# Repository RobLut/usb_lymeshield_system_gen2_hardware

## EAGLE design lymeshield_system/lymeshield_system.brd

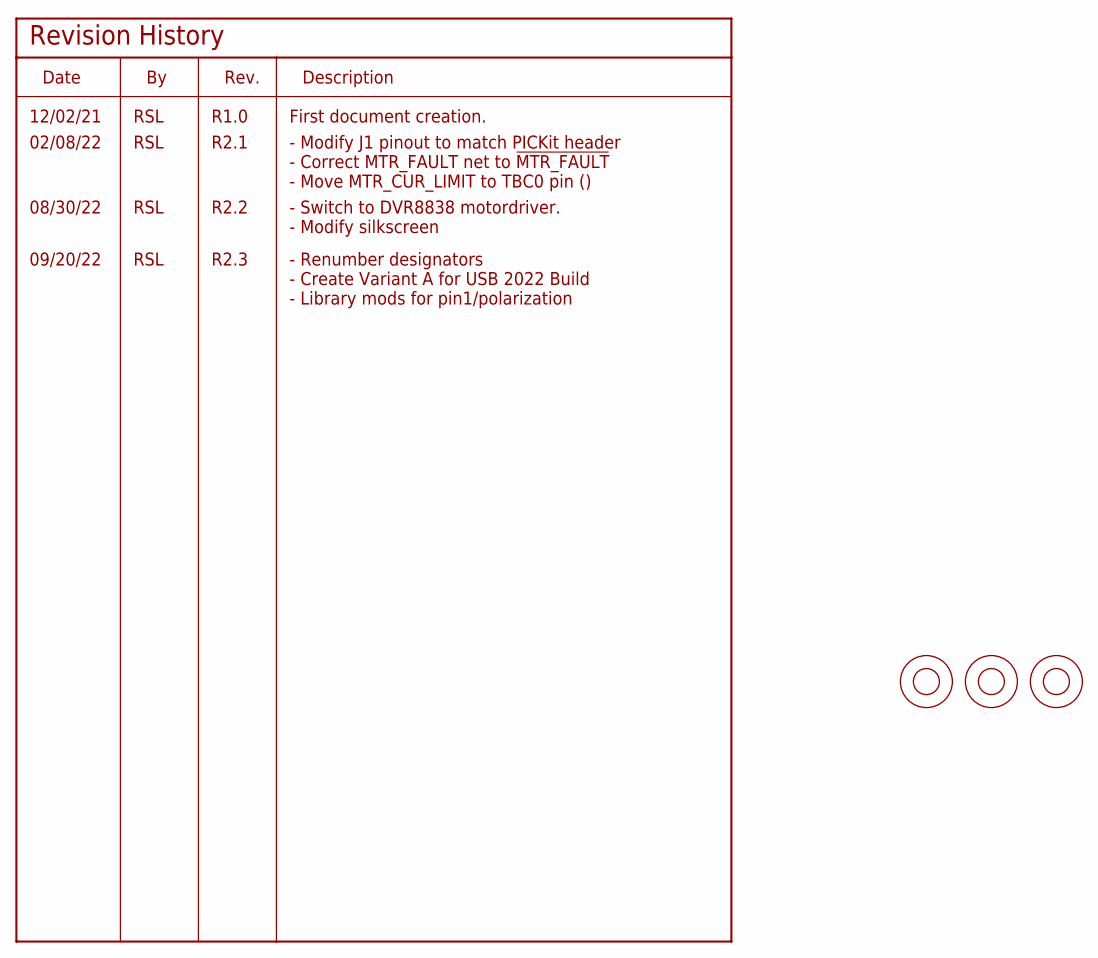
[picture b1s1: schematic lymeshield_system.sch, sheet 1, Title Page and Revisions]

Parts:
FID1, FID2, FID3: FIDUCIAL_1MM_TOP_BOTTOM

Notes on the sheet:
12/02/21
RSL
R1.0
First document creation.
02/08/22
R2.1
- Modify J1 pinout to match PICKit header - Correct MTR_FAULT net to !MTR_FAULT - Move MTR_CUR_LIMIT to TBC0 pin ()
08/30/22
R2.2
- Switch to DVR8838 motordriver. - Modify silkscreen
09/20/22
R2.3
- Renumber designators - Create Variant A for USB 2022 Build - Library mods for pin1/polarization

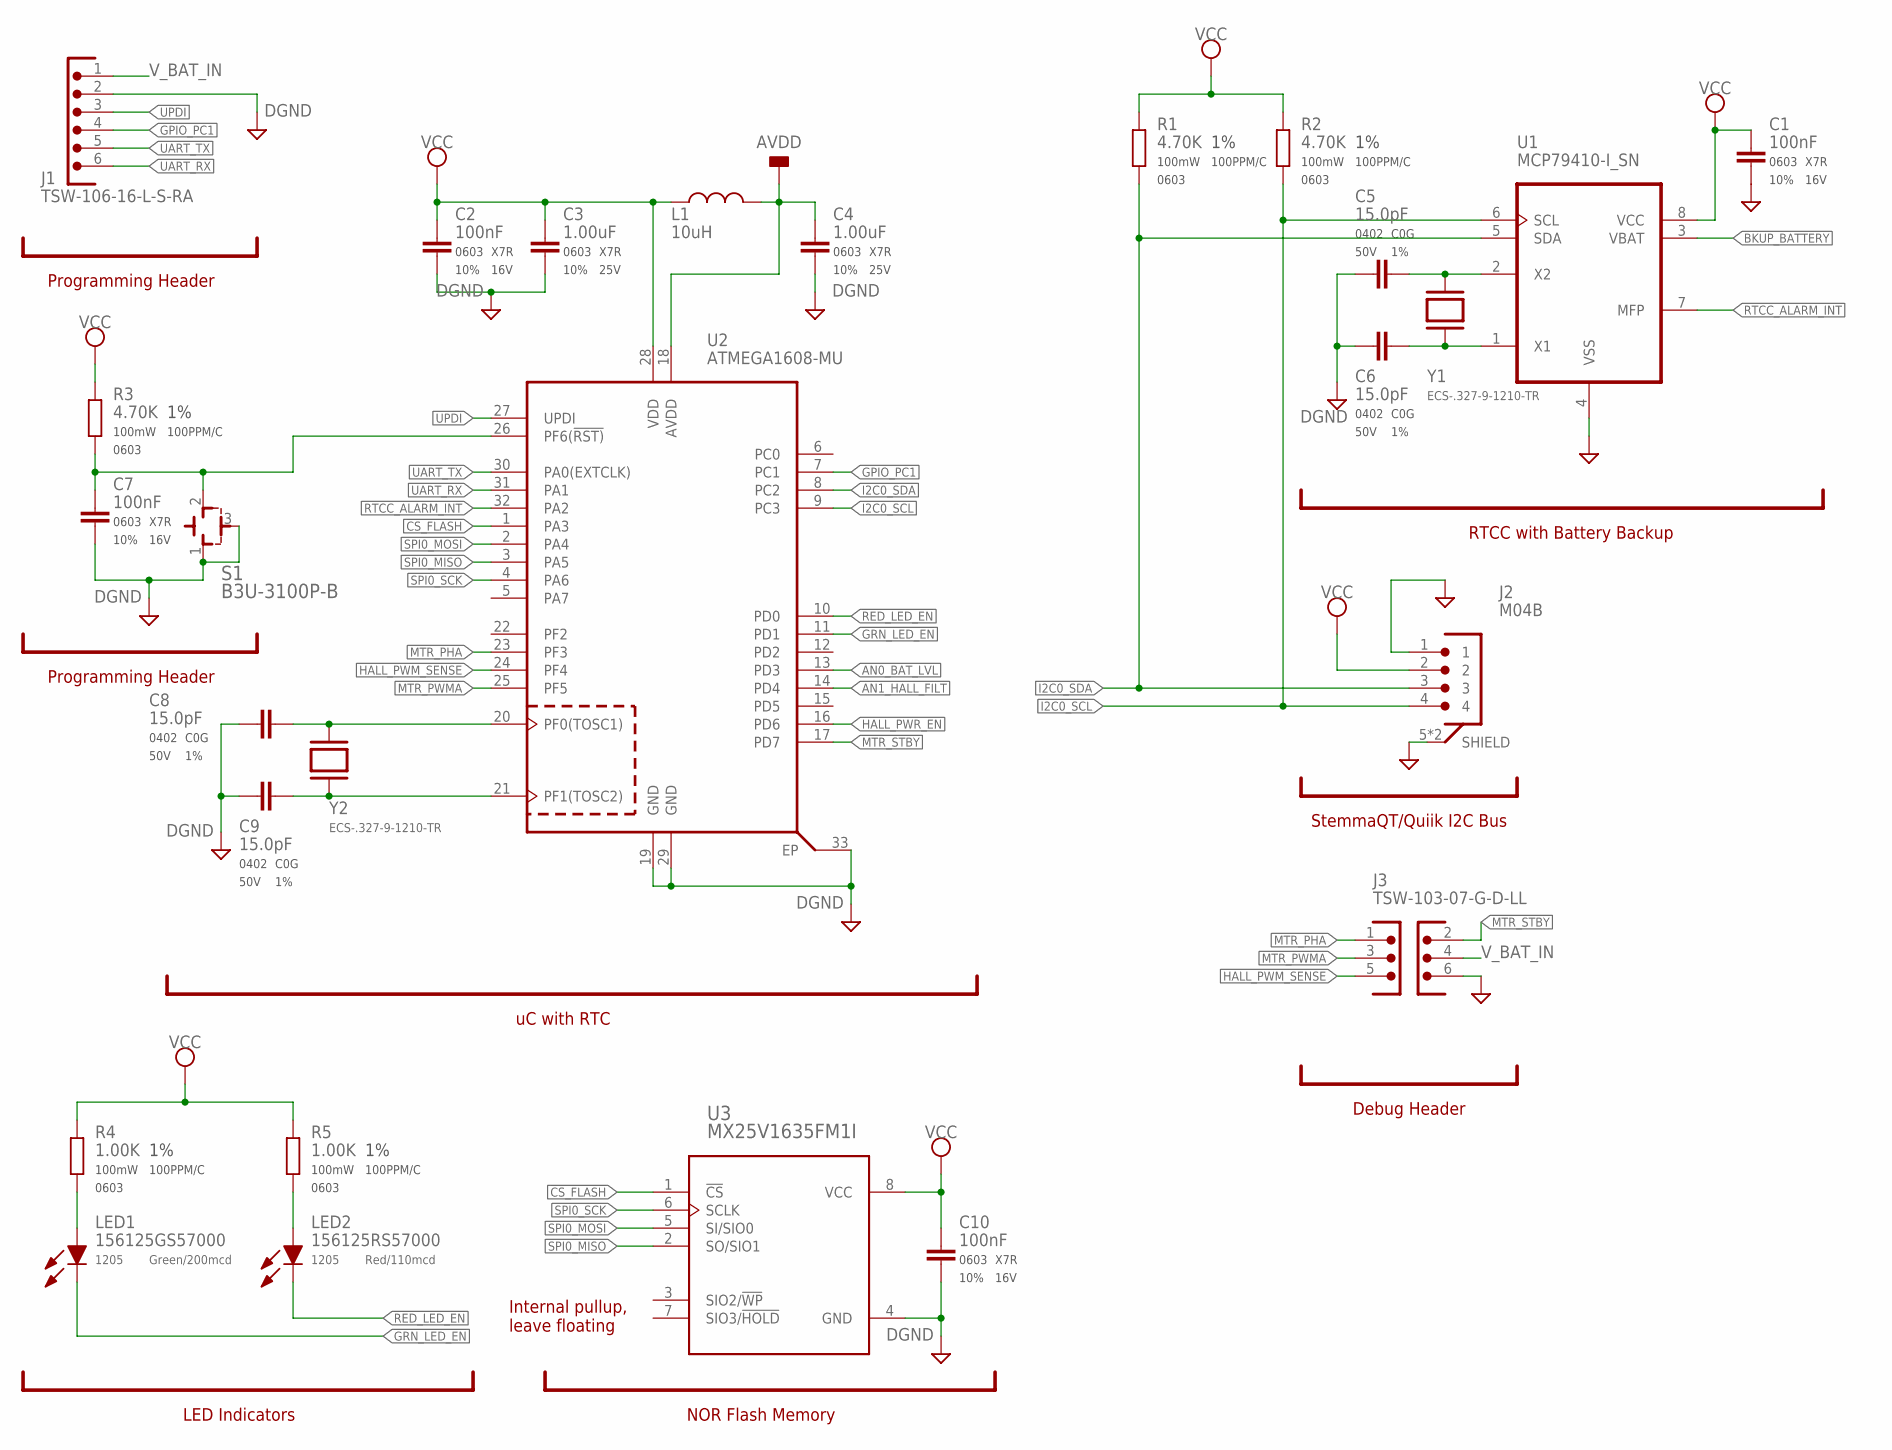
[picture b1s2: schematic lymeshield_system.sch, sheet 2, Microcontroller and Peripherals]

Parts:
C1, C2, C7, C10: 100nF; CAPC_0603_1608X90N
C3, C4: 1.00uF; CAPC_0603_1608X90N
C5, C6, C8, C9: 15.0pF; CAPC_0402_1005X55N
J1: TSW-106-16-L-S-RA; HDR-100MIL-1X6-THRU-RA
J2: M04B; SM04B-SRSS-TB(LFSN)
J3: TSW-103-07-G-D-LL; HDRV6W64P254_2X3_762X495X838P
L1: 10uH; INDC1608X90N
LED1: 156125GS57000; LEDC3212X120N
LED2: 156125RS57000; LEDC3212X120N
R1, R2, R3: 4.70K; R0603K
R4, R5: 1.00K; R0603K
S1: B3U-3100P-B
U1: MCP79410-I_SN; SOIC127P600X175-8N
U2: ATMEGA1608-MU; QFN50P500X500X90-33N
U3: MX25V1635FM1I; SOIC127P600X175-8N
Y1, Y2: ECS-.327-9-1210-TR; XTAL_ECS-.327-9-1210-TR

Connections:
!CS_FLASH: U2.1 (PA3), U3.1 (!CS)
!GRN_LED_EN: LED1.1 (K), U2.11 (PD1)
!MTR_STBY: J3.2, U2.17 (PD7); also elsewhere on the board
!RED_LED_EN: LED2.1 (K), U2.10 (PD0)
!RST: C7.1, R3.2, S1.2 (NO), U2.26 (PF6(!RST))
AN0_BAT_LVL: U2.13 (PD3); also elsewhere on the board
AN1_HALL_FILT: U2.14 (PD4); also elsewhere on the board
AVDD: C4.1, L1.2, U2.18 (AVDD)
BKUP_BATTERY: U1.3 (VBAT); also elsewhere on the board
DGND: C1.2, C2.2, C3.2, C4.2, C5.2, C6.2, C7.2, C8.2, C9.2, C10.2, J1.2, J2.1, J2.5 (SHIELD), J2.6 (SHIELD), J3.6, S1.1 (COM), S1.3 (COM1), U1.4 (VSS), U2.19 (GND), U2.29 (GND), U2.33 (EP), U3.4 (GND); also elsewhere on the board
GPIO_PC1: J1.4, U2.7 (PC1)
HALL_PWM_SENSE: J3.5, U2.24 (PF4); also elsewhere on the board
HALL_PWR_EN: U2.16 (PD6); also elsewhere on the board
I2C0_SCL: J2.4, R2.2, U1.6 (SCL), U2.9 (PC3)
I2C0_SDA: J2.3, R1.2, U1.5 (SDA), U2.8 (PC2)
MTR_PHA: J3.1, U2.23 (PF3); also elsewhere on the board
MTR_PWMA: J3.3, U2.25 (PF5); also elsewhere on the board
unnamed: C8.1, U2.20 (PF0(TOSC1)), Y2.1
unnamed: C5.1, U1.2 (X2), Y1.1
unnamed: LED1.2 (A), R4.2
unnamed: LED2.2 (A), R5.2
unnamed: C9.1, U2.21 (PF1(TOSC2)), Y2.2
unnamed: C6.1, U1.1 (X1), Y1.2
RTCC_ALARM_INT: U1.7 (MFP), U2.32 (PA2)
SPI0_MISO: U2.3 (PA5), U3.2 (SO/SIO1)
SPI0_MOSI: U2.2 (PA4), U3.5 (SI/SIO0)
SPI0_SCK: U2.4 (PA6), U3.6 (SCLK)
UART_RX: J1.6, U2.31 (PA1)
UART_TX: J1.5, U2.30 (PA0(EXTCLK))
UPDI: J1.3, U2.27 (UPDI)
VCC: C1.1, C2.1, C3.1, C10.1, J2.2, L1.1, R1.1, R2.1, R3.1, R4.1, R5.1, U1.8 (VCC), U2.28 (VDD), U3.8 (VCC); also elsewhere on the board
V_BAT_IN: J1.1, J3.4; also elsewhere on the board

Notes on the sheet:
Internal pullup, leave floating
StemmaQT/Quiik I2C Bus
NOR Flash Memory
RTCC with Battery Backup
Programming Header
LED Indicators
uC with RTC
Debug Header

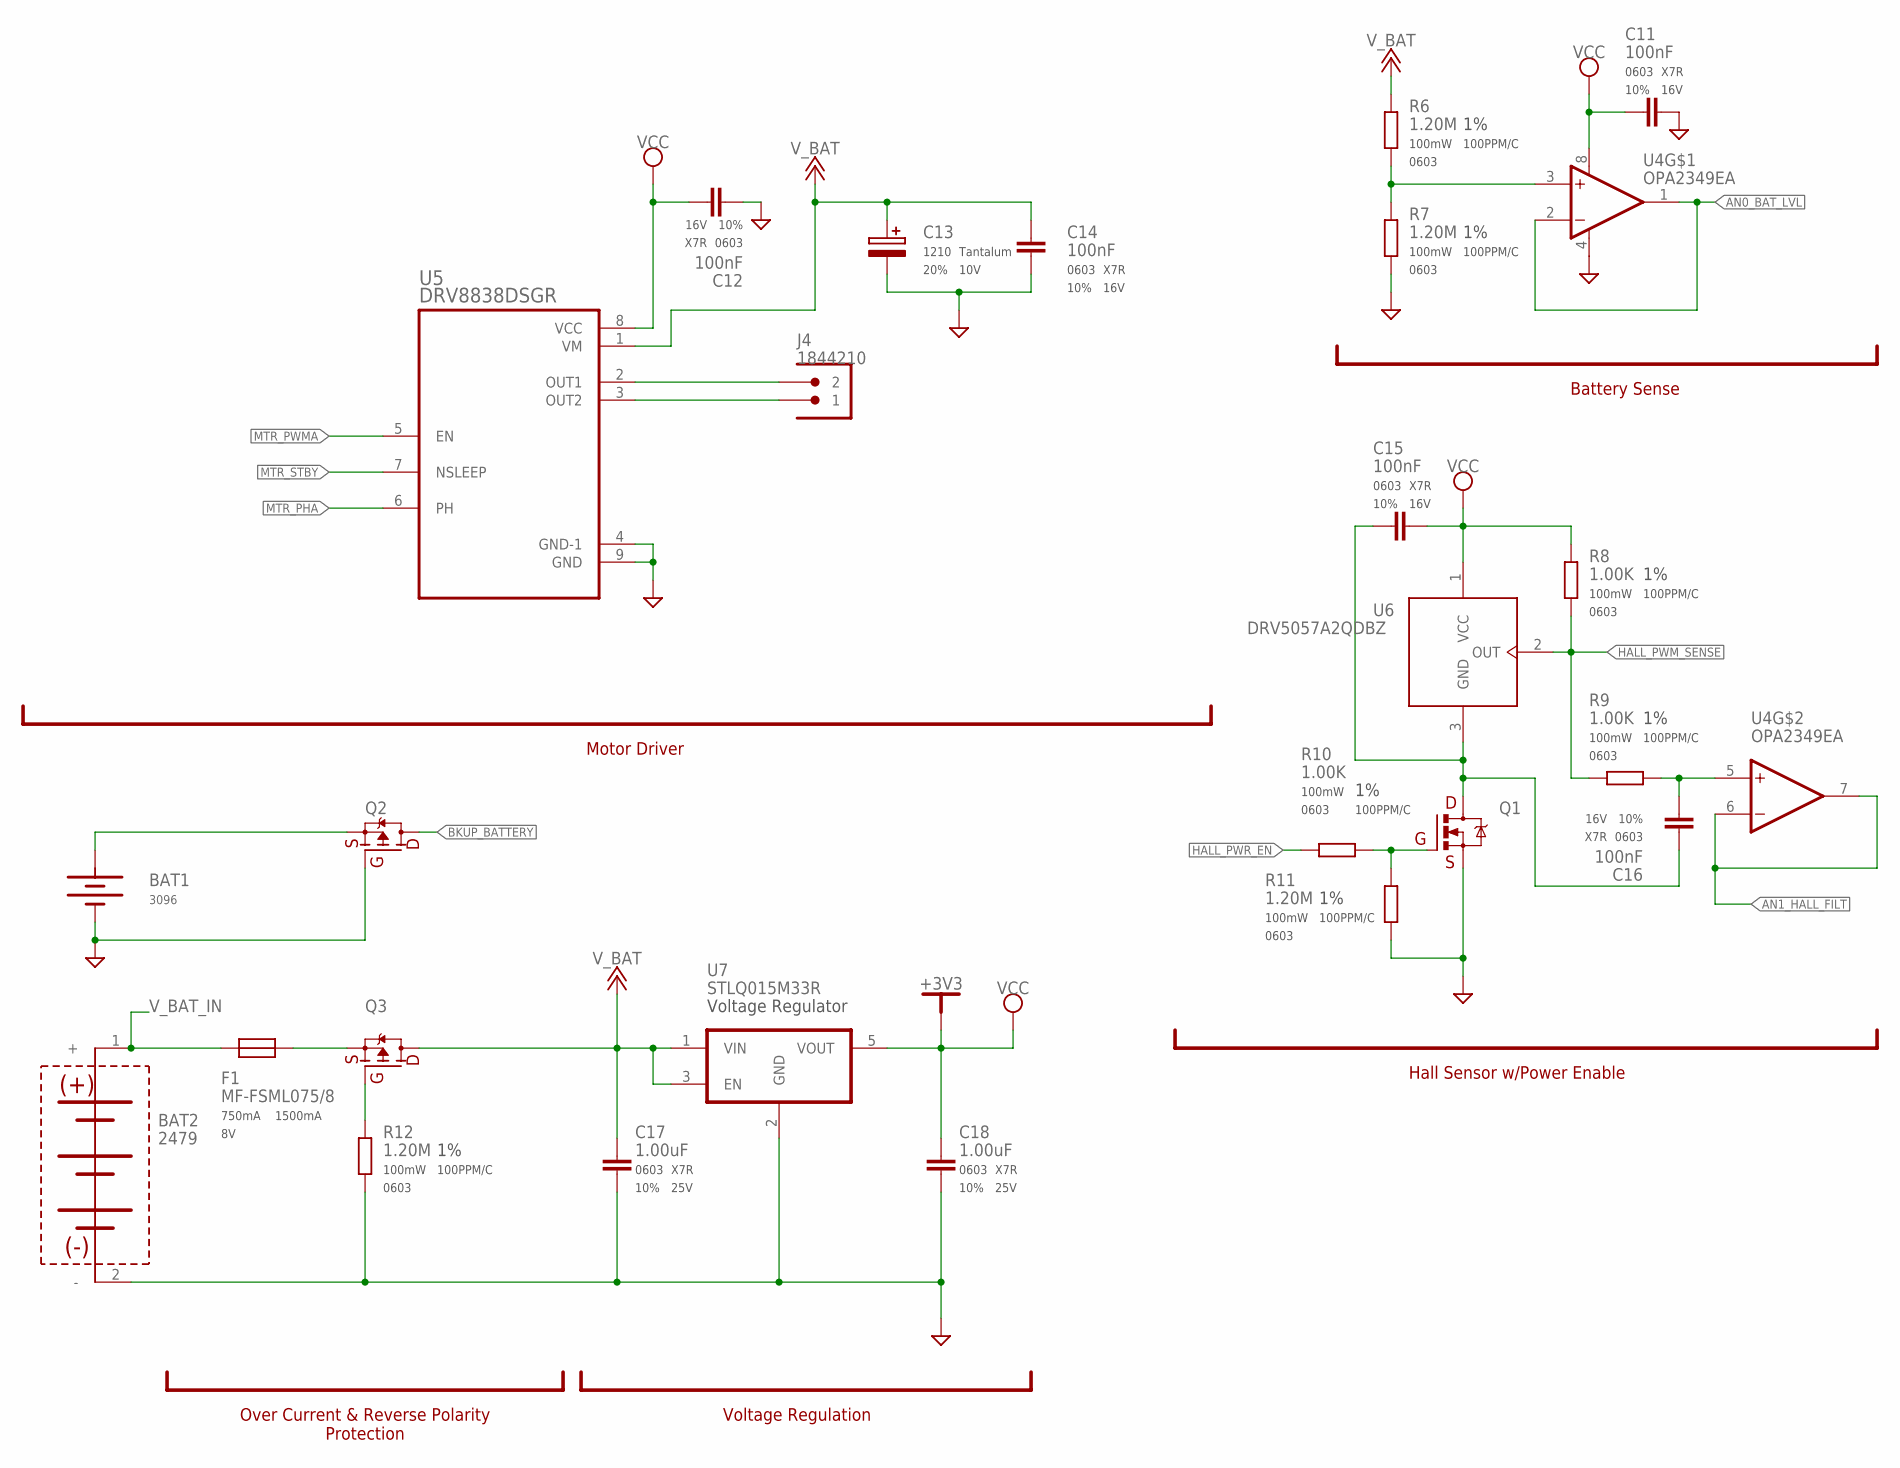
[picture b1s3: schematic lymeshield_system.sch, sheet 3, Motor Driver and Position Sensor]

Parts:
BAT1: 3096
BAT2: 2479
C11, C12, C14, C15, C16: 100nF; CAPC_0603_1608X90N
C13: TAJB226M010RNJ; PCAPC_1210
C17, C18: 1.00uF; CAPC_0603_1608X90N
F1: MF-FSML075/8; FUSC1608X70N
J4: 1844210; 1844210-2-3.50
Q1: FDN5632N-F085-FDN5632N_F085; SOT-23
Q2, Q3: PMOS_DMP2035U-7; SOT-23
R6, R7, R11, R12: 1.20M; R0603K
R8, R9, R10: 1.00K; R0603K
U4: OPA2349EA; SOT65P280X145-8N
U5: DRV8838DSGR; SON50P200X200X80-9N
U6: DRV5057A2QDBZ; SOT95P237X112-3N
U7: STLQ015M33R; SOT23-5L

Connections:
!MTR_STBY: U5.7 (NSLEEP); also elsewhere on the board
AN0_BAT_LVL: U4.1 (OUT), U4.2 (-IN); also elsewhere on the board
AN1_HALL_FILT: U4.6 (-IN), U4.7 (OUT); also elsewhere on the board
BKUP_BATTERY: Q2.1 (D); also elsewhere on the board
DGND: BAT1.1 (-), BAT1.3 (-), BAT2.2 (-), C11.1, C12.2, C13.2 (-), C14.2, C17.2, C18.2, Q1.2 (S), Q2.3 (G), R7.2, R11.2, R12.2, U4.4 (V-), U5.4 (GND-1), U5.9 (GND), U7.2 (GND); also elsewhere on the board
HALL_PWM_SENSE: R8.2, R9.1, U6.2 (OUT); also elsewhere on the board
HALL_PWR_EN: R10.1; also elsewhere on the board
MTR_PHA: U5.6 (PH); also elsewhere on the board
MTR_PWMA: U5.5 (EN); also elsewhere on the board
unnamed: Q1.3 (G), R10.2, R11.1
unnamed: Q3.3 (G), R12.1
unnamed: BAT1.2 (+), Q2.2 (S)
unnamed: R6.2, R7.1, U4.3 (+IN)
unnamed: F1.2, Q3.2 (S)
unnamed: C16.1, R9.2, U4.5 (+IN)
unnamed: C15.2, C16.2, Q1.1 (D), U6.3 (GND)
OUTA1: J4.P$2 (2), U5.2 (OUT1)
OUTA2: J4.P$1 (1), U5.3 (OUT2)
VCC: C11.2, C12.1, C15.1, C18.1, R8.1, U4.8 (V+), U5.8 (VCC), U6.1 (VCC), U7.5 (VOUT); also elsewhere on the board
V_BAT: C13.1 (+), C14.1, C17.1, Q3.1 (D), R6.1, U5.1 (VM), U7.1 (VIN), U7.3 (EN)
V_BAT_IN: BAT2.1 (+), F1.1; also elsewhere on the board

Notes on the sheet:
Hall Sensor w/Power Enable
Voltage Regulation
Over Current & Reverse Polarity Protection
Motor Driver
Battery Sense

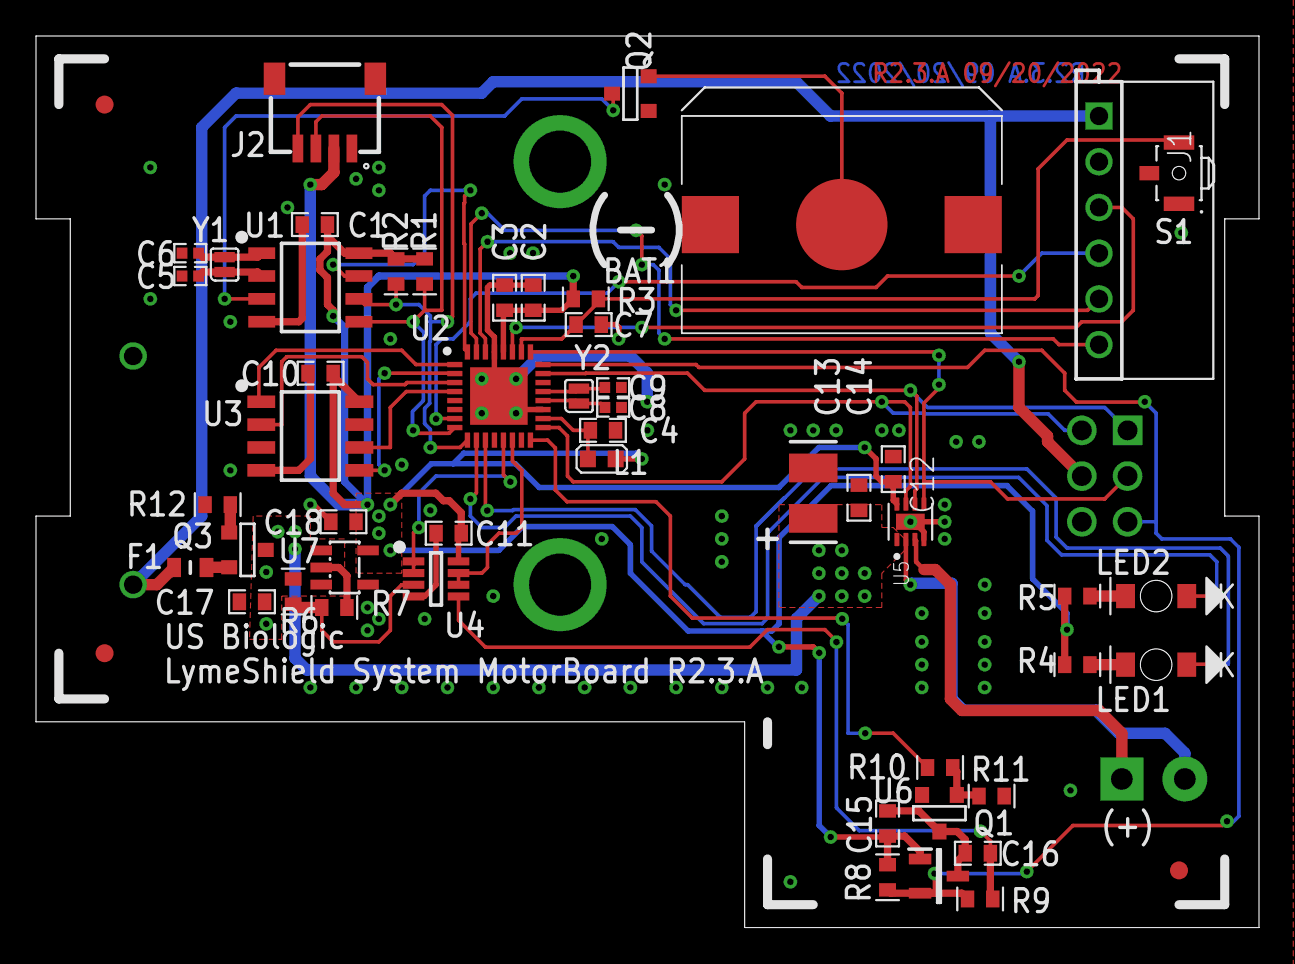
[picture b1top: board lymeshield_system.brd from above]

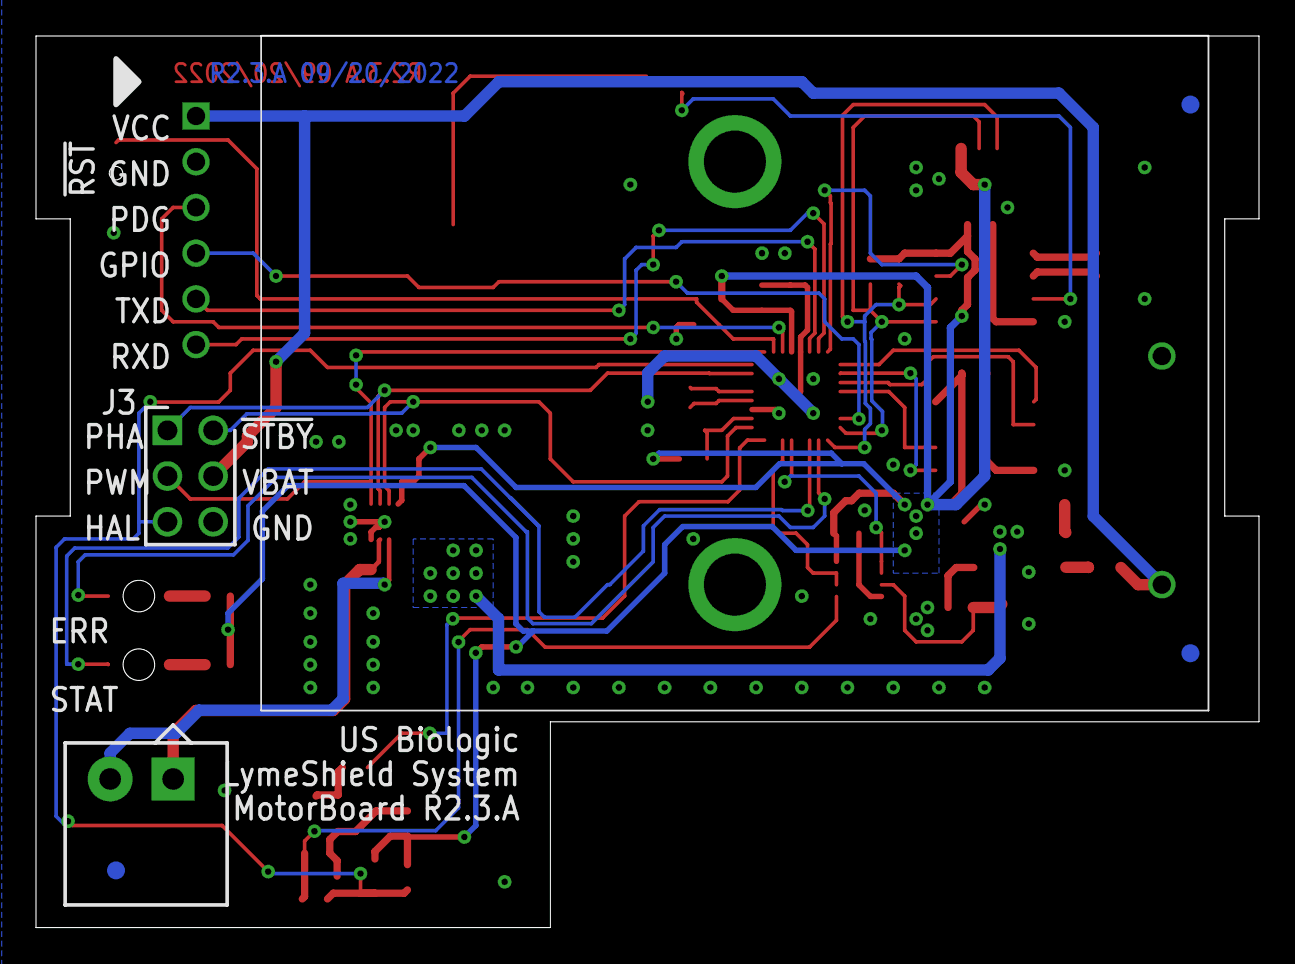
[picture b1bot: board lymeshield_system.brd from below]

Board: 2 copper layers, 67.9 x 49.5 mm, 56 parts (3 on the bottom side), 42 nets.

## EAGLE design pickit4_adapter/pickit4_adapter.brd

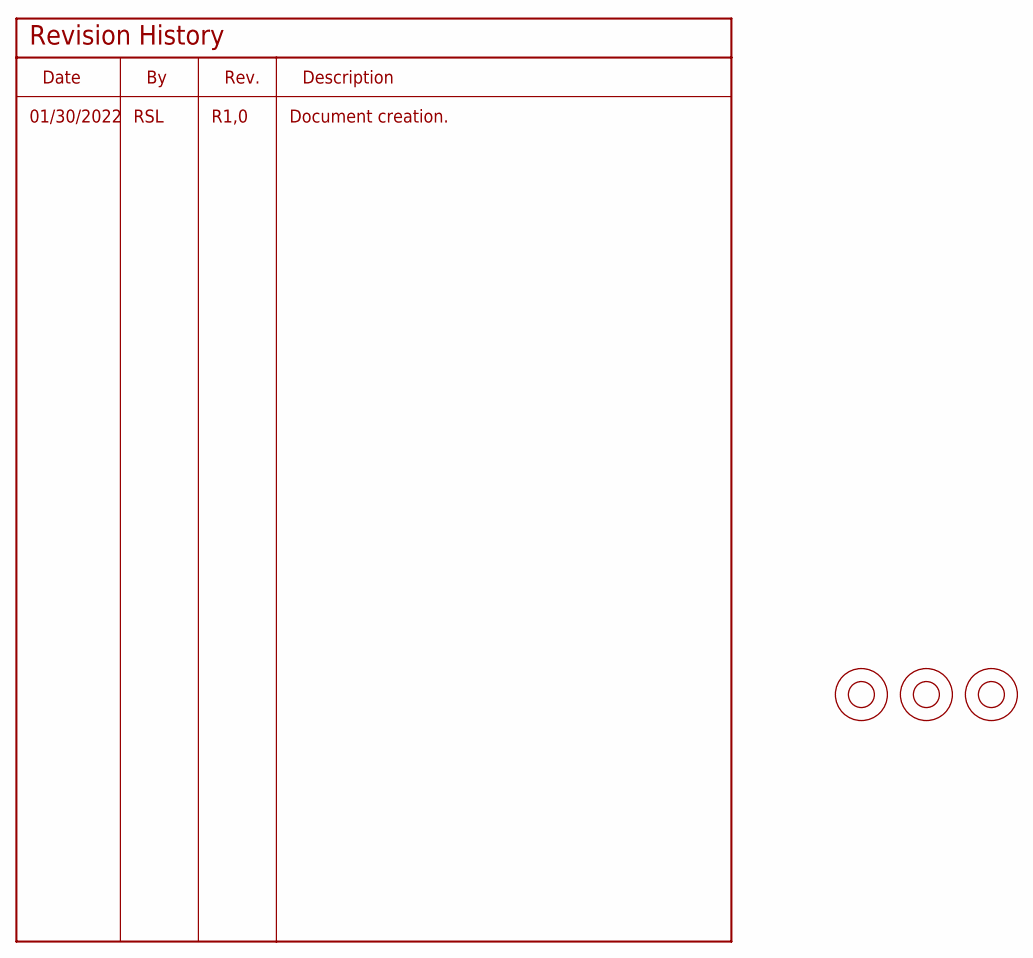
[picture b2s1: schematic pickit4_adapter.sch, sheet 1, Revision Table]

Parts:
FID1, FID2, FID3: FIDUCIAL_1MM_TOP_BOTTOM

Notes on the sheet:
01/30/2022
RSL
R1,0
Document creation.

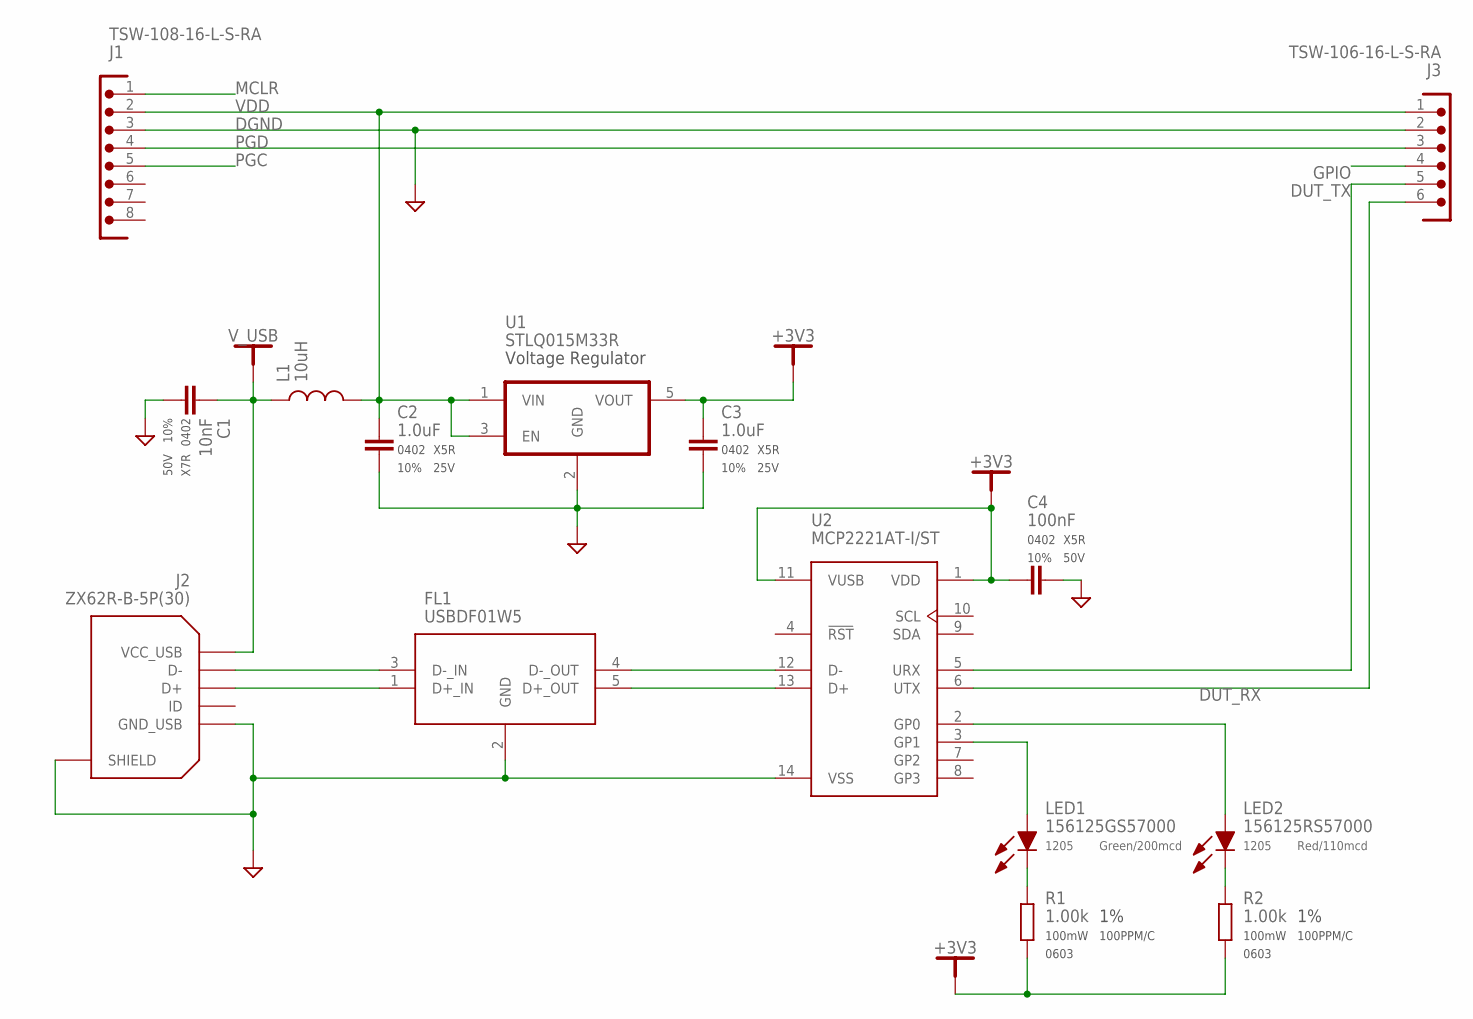
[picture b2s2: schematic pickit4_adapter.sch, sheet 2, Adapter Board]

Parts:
C1: 10nF; CAPC_0402_1005X55N
C2, C3: 1.0uF; CAPC_0402_1005X55N
C4: 100nF; CAPC_0402_1005X55N
FL1: USBDF01W5; SOT65P210X110-5N
J1: TSW-108-16-L-S-RA; HDR-100MIL-1X8-THRU-RA
J2: ZX62R-B-5P(30)
J3: TSW-106-16-L-S-RA; HDR-100MIL-1X6-THRU-RA
L1: 10uH; INDC1608X90N
LED1: 156125GS57000; LEDC3212X120N
LED2: 156125RS57000; LEDC3212X120N
R1, R2: 1.00k; R0603K
U1: STLQ015M33R; SOT23-5L
U2: MCP2221AT-I/ST; SOP65P640X120-14N

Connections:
+3V3: C3.1, C4.1, R1.2, R2.2, U1.5 (VOUT), U2.1 (VDD), U2.11 (VUSB)
DGND: C1.2, C2.2, C3.2, C4.2, FL1.2 (GND), J1.3, J2.5 (GND_USB), J2.6 (SHIELD), J2.7 (SHIELD), J2.8 (SHIELD), J2.9 (SHIELD), J2.10 (SHIELD), J2.11 (SHIELD), J3.2, U1.2 (GND), U2.14 (VSS)
DUT_RX: J3.6, U2.6 (UTX)
DUT_TX: J3.5, U2.5 (URX)
GPIO: J3.4
MCLR: J1.1
unnamed: FL1.4 (D-_OUT), U2.12 (D-)
unnamed: FL1.5 (D+_OUT), U2.13 (D+)
unnamed: FL1.3 (D-_IN), J2.2 (D-)
unnamed: FL1.1 (D+_IN), J2.3 (D+)
unnamed: LED2.2 (A), U2.2 (GP0)
unnamed: LED1.2 (A), U2.3 (GP1)
unnamed: LED1.1 (K), R1.1
unnamed: LED2.1 (K), R2.1
PGC: J1.5
PGD: J1.4, J3.3
VDD: C2.1, J1.2, J3.1, L1.2, U1.1 (VIN), U1.3 (EN)
V_USB: C1.1, J2.1 (VCC_USB), L1.1

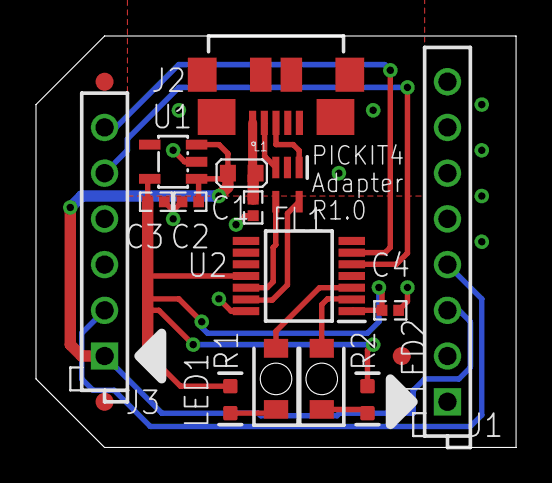
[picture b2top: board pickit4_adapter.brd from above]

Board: 2 copper layers, 26.7 x 22.9 mm, 18 parts (0 on the bottom side), 15 nets.

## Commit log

2022-02-03 refactor: added existing project files for first commit
2022-02-03 refactor: fixed ignored files and added tables
2022-02-03 refactor: rename cam files to match release tag
2022-02-09 feat: partial changes for r1,1 - Moved cur_limit to TBC0 pin - Modify layout to reduce EMI - Change programming header to match PICKit4 - Merge mtr_cur_limit into !mtr_cur_limit net
2022-02-13 fix: updates for R2.1 board - Change layout for high current routes - Correct routing errors (mtr_cur_limit) - Change tantalum cap to 1210 and give more space
2022-09-13 fix(lss): update to R2.2 - Change motor driver
2022-09-21 fix (schematics/layout): update for 2.3.a build - Add variant "A" to schematics - Modify footprints for polarization - Update silkscreen for 2.3.a

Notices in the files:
parts and their libraries:
HatchPoint-Wurtz: Copyright: Würth Elektronik
